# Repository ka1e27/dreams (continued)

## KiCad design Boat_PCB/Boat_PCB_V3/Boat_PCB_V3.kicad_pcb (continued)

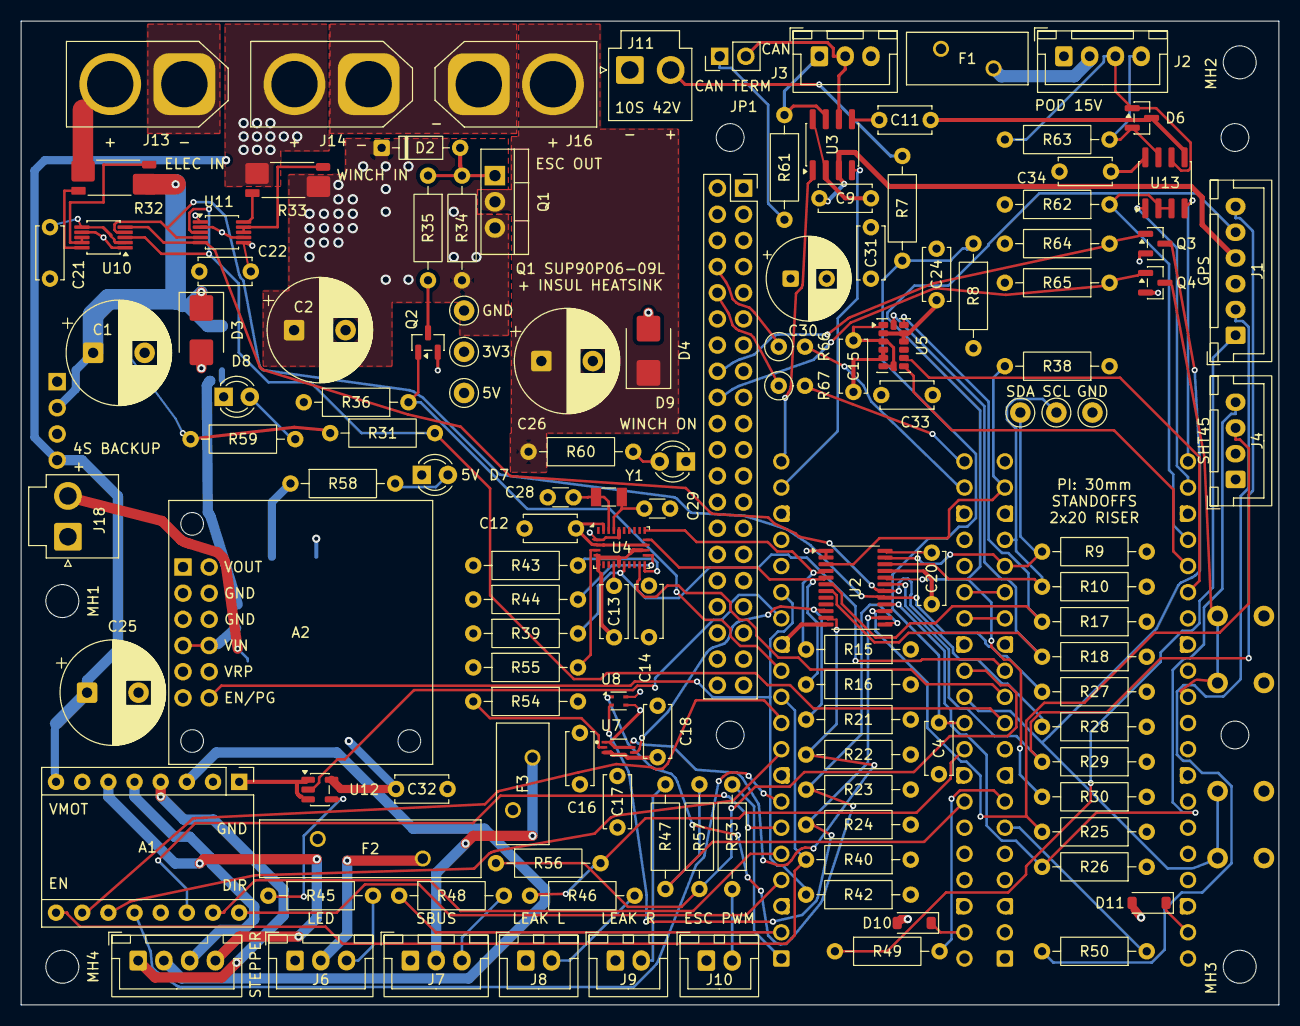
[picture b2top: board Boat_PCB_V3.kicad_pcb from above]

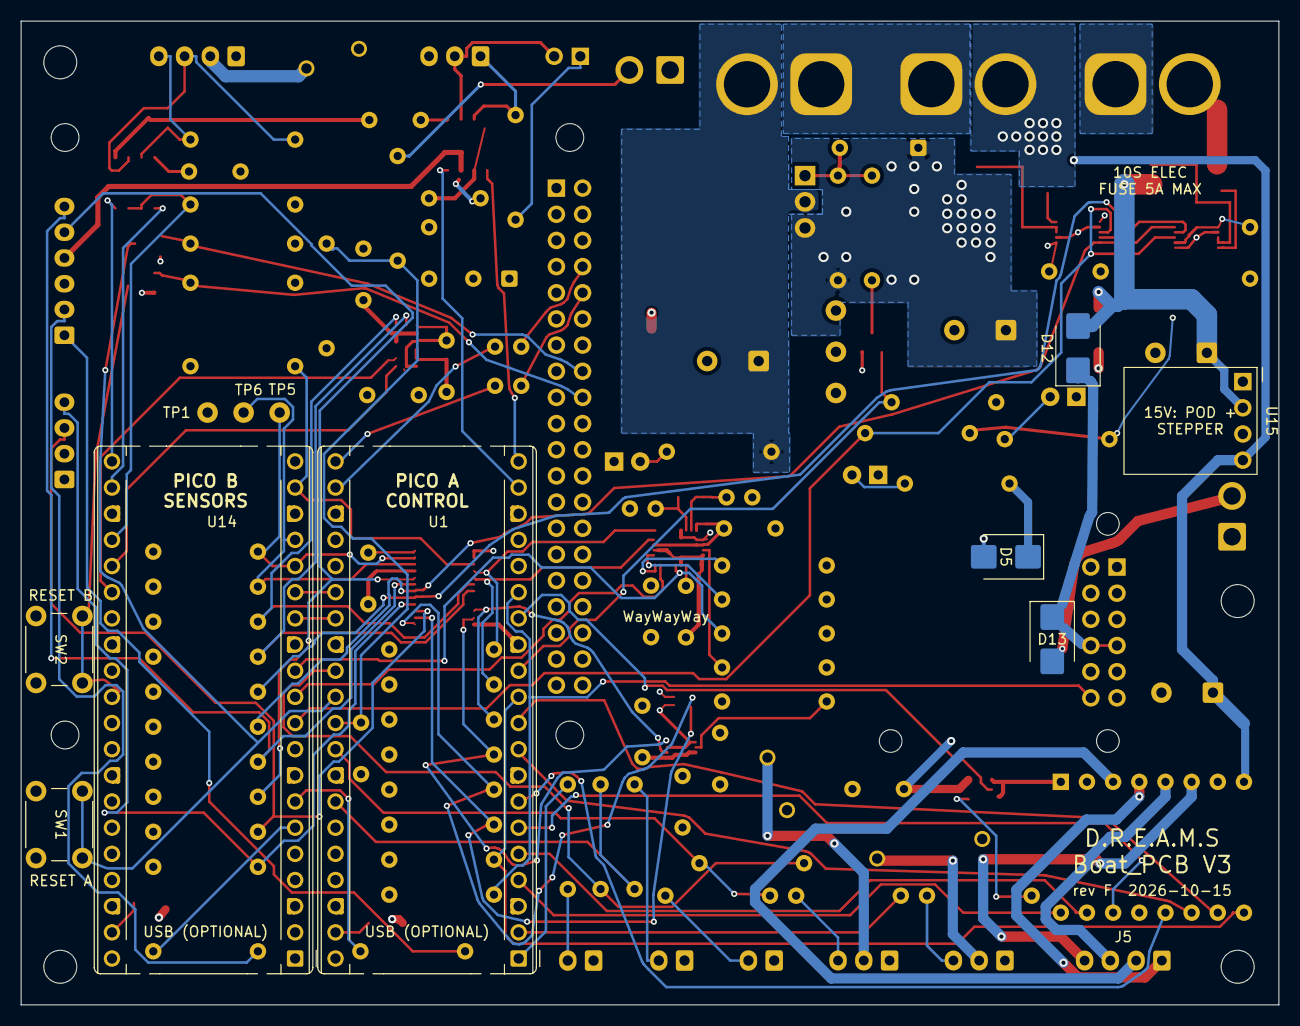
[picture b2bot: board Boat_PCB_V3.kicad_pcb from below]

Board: 4 copper layers, 122.1 x 95.5 mm, 140 parts (8 on the bottom side), 105 nets.

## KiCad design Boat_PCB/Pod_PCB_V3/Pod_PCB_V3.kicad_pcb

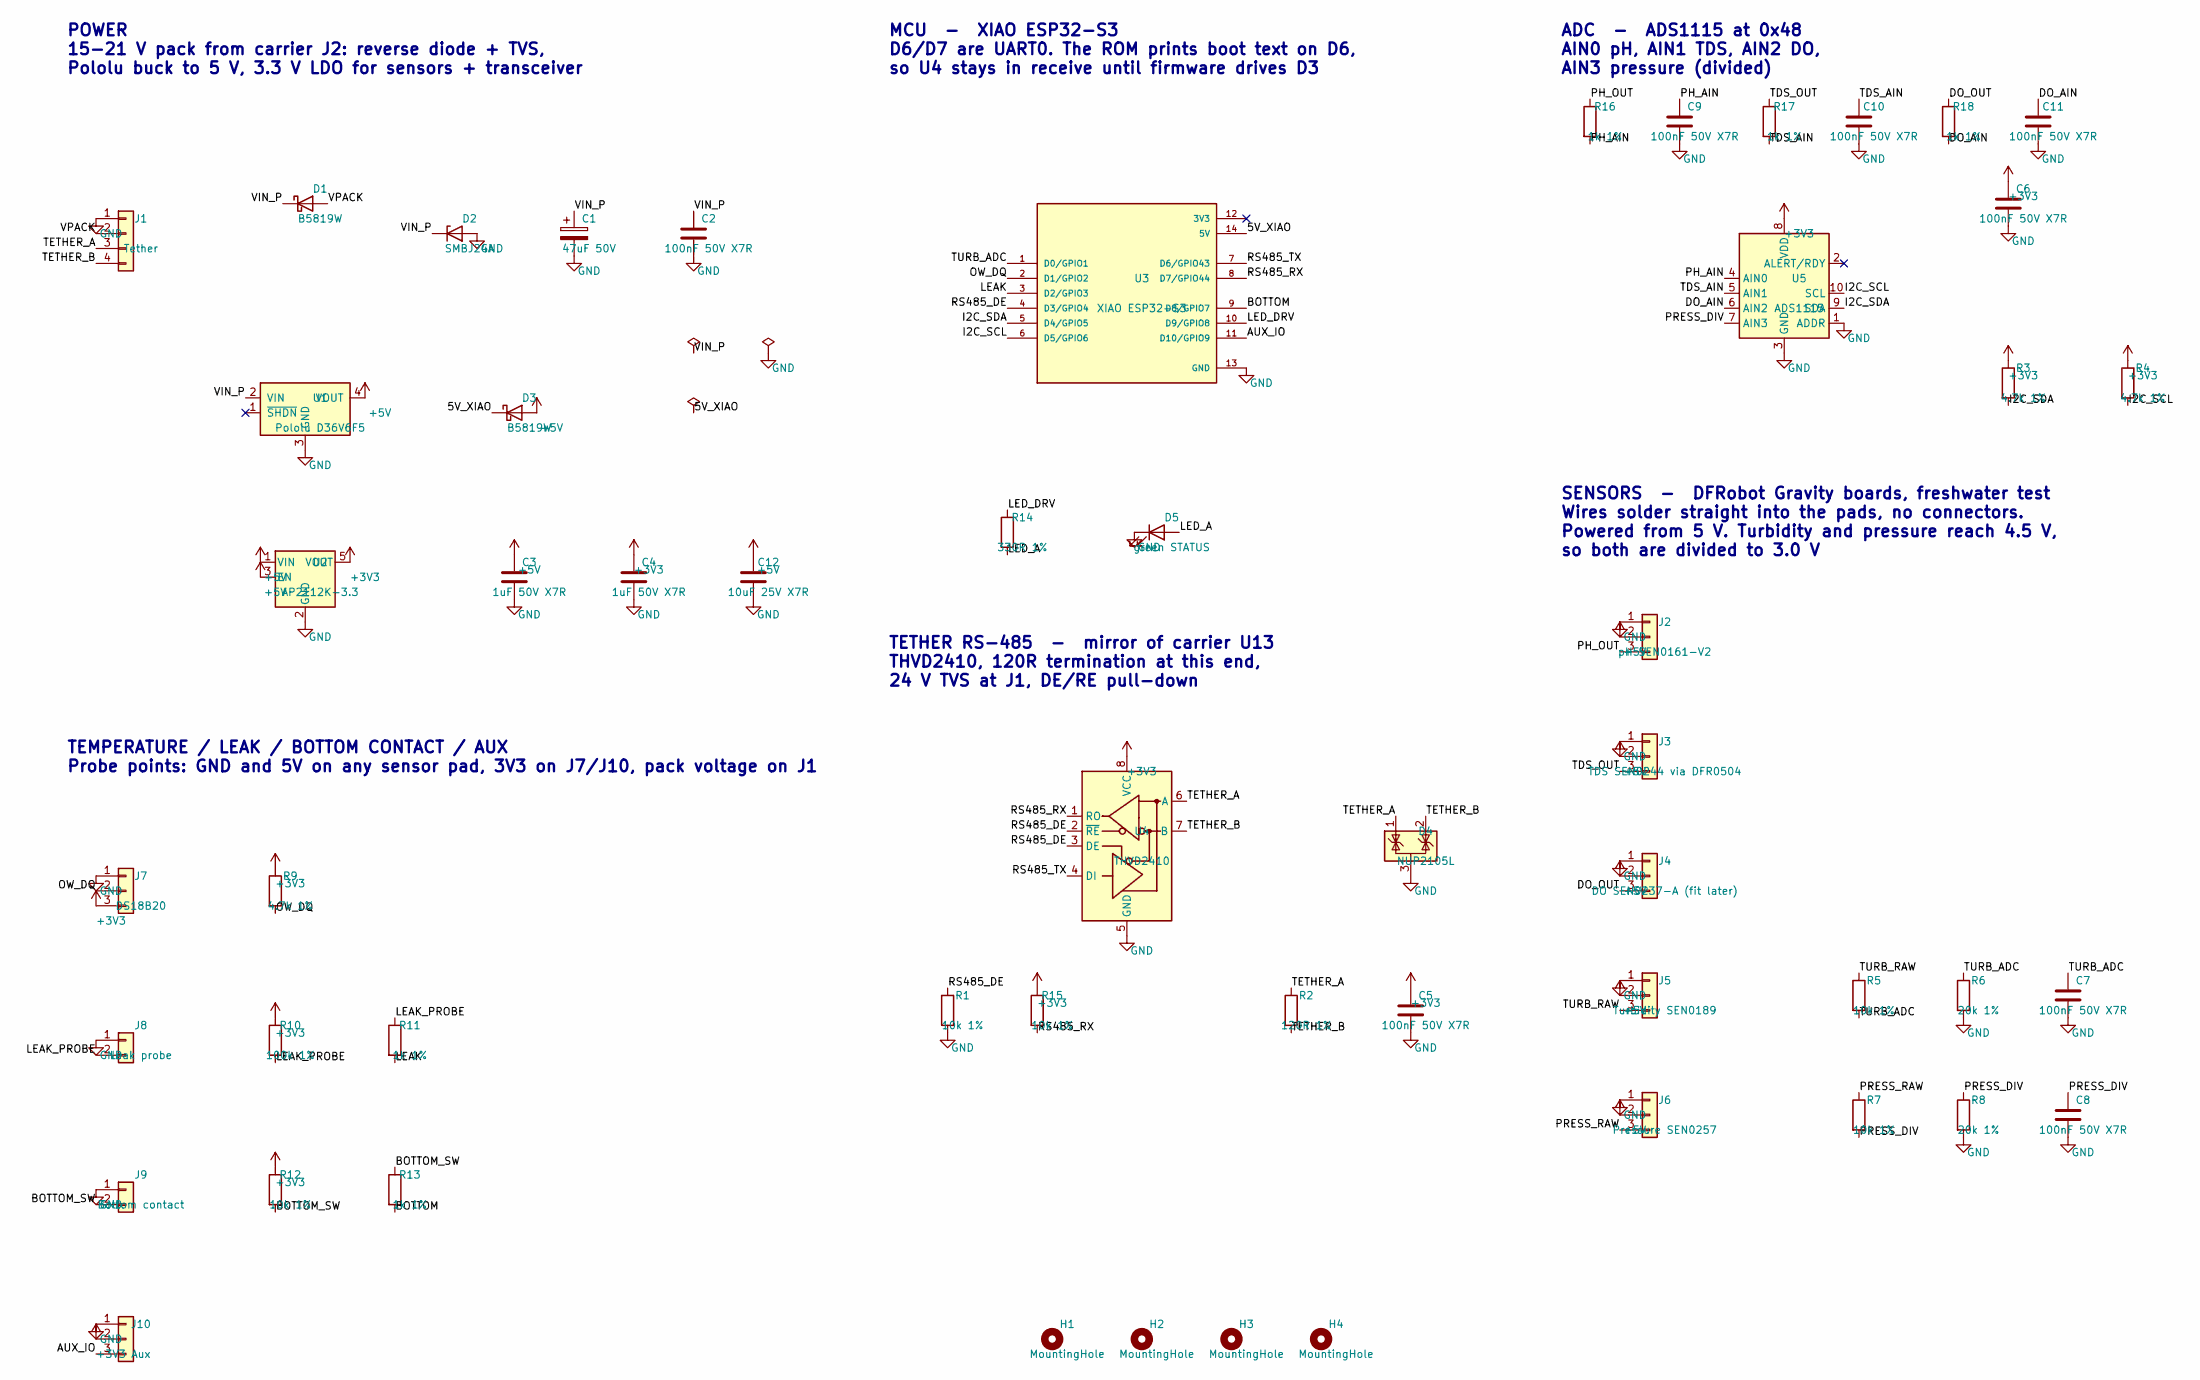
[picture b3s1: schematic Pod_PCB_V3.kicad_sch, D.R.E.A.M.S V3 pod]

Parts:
C1: 47uF 50V; CP_Radial_D6.3mm_P2.50mm
C2, C5, C6, C7, C8, C9, C10, C11: 100nF 50V X7R; C_Disc_D5.0mm_W2.5mm_P5.00mm
C3, C4: 1uF 50V X7R; C_Disc_D5.0mm_W2.5mm_P5.00mm
C12: 10uF 25V X7R; C_Disc_D5.0mm_W2.5mm_P5.00mm
D1, D3: B5819W; D_SOD-123
D2: SMBJ24A; D_SMB
D4: NUP2105L; SOT-23
D5: green STATUS; LED_D3.0mm
H1, H2, H3, H4: MountingHole; MountingHole_3.2mm_M3
J1: Tether; SolderWire_1x04_P2.54mm_D1.0mm
J2: pH SEN0161-V2; SolderWire_1x03_P2.54mm_D1.0mm
J3: TDS SEN0244 via DFR0504; SolderWire_1x03_P2.54mm_D1.0mm
J4: DO SEN0237-A (fit later); SolderWire_1x03_P2.54mm_D1.0mm
J5: Turbidity SEN0189; SolderWire_1x03_P2.54mm_D1.0mm
J6: Pressure SEN0257; SolderWire_1x03_P2.54mm_D1.0mm
J7: DS18B20; SolderWire_1x03_P2.54mm_D1.0mm
J8: Leak probe; SolderWire_1x02_P2.54mm_D1.0mm
J9: Bottom contact; SolderWire_1x02_P2.54mm_D1.0mm
J10: Aux; SolderWire_1x03_P2.54mm_D1.0mm
R1, R5, R7, R12, R15: 10k 1%; R_Axial_DIN0207_L6.3mm_D2.5mm_P10.16mm_Horizontal
R2: 120R 1%; R_Axial_DIN0207_L6.3mm_D2.5mm_P10.16mm_Horizontal
R3, R4, R9: 4.7k 1%; R_Axial_DIN0207_L6.3mm_D2.5mm_P10.16mm_Horizontal
R6, R8: 20k 1%; R_Axial_DIN0207_L6.3mm_D2.5mm_P10.16mm_Horizontal
R10: 100k 1%; R_Axial_DIN0207_L6.3mm_D2.5mm_P10.16mm_Horizontal
R11, R13, R16, R17, R18: 1k 1%; R_Axial_DIN0207_L6.3mm_D2.5mm_P10.16mm_Horizontal
R14: 330R 1%; R_Axial_DIN0207_L6.3mm_D2.5mm_P10.16mm_Horizontal
U1: Pololu D36V6F5; Pololu_D36V6F5
U2: AP2112K-3.3; SOT-23-5
U3: XIAO ESP32-S3; MODULE_XIAO_ESP32_S3
U4: THVD2410; SOIC-8_3.9x4.9mm_P1.27mm
U5: ADS1115; MSOP-10_3x3mm_P0.5mm

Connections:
+3V3: C4.1, C5.1, C6.1, J7.3 (VDD), J10.2 (3V3), R3.1, R4.1, R9.1, R10.1, R12.1, R15.1, U2.5 (VOUT), U4.8 (VCC), U5.8 (VDD)
+5V: C3.1, C12.1, D3.2 (A), J2.2 (VCC), J3.2 (VCC), J4.2 (VCC), J5.2 (VCC), J6.2 (VCC), U1.4 (VOUT), U2.1 (VIN), U2.3 (EN)
/5V_XIAO: D3.1 (K), U3.14 (5V)
/AUX_IO: J10.3 (IO), U3.11 (D10/GPIO9)
/BOTTOM: R13.2, U3.9 (D8/GPIO7)
/BOTTOM_SW: J9.2 (SW), R12.2, R13.1
/DO_AIN: C11.1, R18.2, U5.6 (AIN2)
/DO_OUT: J4.3 (SIG), R18.1
/I2C_SCL: R4.2, U3.6 (D5/GPIO6), U5.10 (SCL)
/I2C_SDA: R3.2, U3.5 (D4/GPIO5), U5.9 (SDA)
/LEAK: R11.2, U3.3 (D2/GPIO3)
/LEAK_PROBE: J8.2 (LEAK), R10.2, R11.1
/LED_A: D5.2 (A), R14.2
/LED_DRV: R14.1, U3.10 (D9/GPIO8)
/OW_DQ: J7.2 (DQ), R9.2, U3.2 (D1/GPIO2)
/PH_AIN: C9.1, R16.2, U5.4 (AIN0)
/PH_OUT: J2.3 (SIG), R16.1
/PRESS_DIV: C8.1, R7.2, R8.1, U5.7 (AIN3)
/PRESS_RAW: J6.3 (SIG), R7.1
/RS485_DE: R1.1, U3.4 (D3/GPIO4), U4.2 (~RE), U4.3 (DE)
/RS485_RX: R15.2, U3.8 (D7/GPIO44), U4.1 (RO)
/RS485_TX: U3.7 (D6/GPIO43), U4.4 (DI)
/TDS_AIN: C10.1, R17.2, U5.5 (AIN1)
/TDS_OUT: J3.3 (SIG), R17.1
/TETHER_A: D4.1 (K), J1.3 (A), R2.1, U4.6 (A)
/TETHER_B: D4.2 (K), J1.4 (B), R2.2, U4.7 (B)
/TURB_ADC: C7.1, R5.2, R6.1, U3.1 (D0/GPIO1)
/TURB_RAW: J5.3 (SIG), R5.1
/VIN_P: C1.1, C2.1, D1.1 (K), D2.1 (K), U1.2 (VIN)
/VPACK: D1.2 (A), J1.2 (VPACK)
GND: C1.2, C2.2, C3.2, C4.2, C5.2, C6.2, C7.2, C8.2, C9.2, C10.2, C11.2, C12.2, D2.2 (A), D4.3 (A), D5.1 (K), J1.1 (GND), J2.1 (GND), J3.1 (GND), J4.1 (GND), J5.1 (GND), J6.1 (GND), J7.1 (GND), J8.1 (GND), J9.1 (GND), J10.1 (GND), R1.2, R6.2, R8.2, U1.3 (GND), U2.2 (GND), U3.13 (GND), U4.5 (GND), U5.1 (ADDR), U5.3 (GND)

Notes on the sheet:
POWER 15-21 V pack from carrier J2: reverse diode + TVS, Pololu buck to 5 V, 3.3 V LDO for sensors + transceiver
MCU - XIAO ESP32-S3 D6/D7 are UART0. The ROM prints boot text on D6, so U4 stays in receive until firmware drives D3
TETHER RS-485 - mirror of carrier U13 THVD2410, 120R termination at this end, 24 V TVS at J1, DE/RE pull-down
ADC - ADS1115 at 0x48 AIN0 pH, AIN1 TDS, AIN2 DO, AIN3 pressure (divided)
SENSORS - DFRobot Gravity boards, freshwater test Wires solder straight into the pads, no connectors. Powered from 5 V. Turbidity and pressure reach 4.5 V, so both are divided to 3.0 V
TEMPERATURE / LEAK / BOTTOM CONTACT / AUX Probe points: GND and 5V on any sensor pad, 3V3 on J7/J10, pack voltage on J1

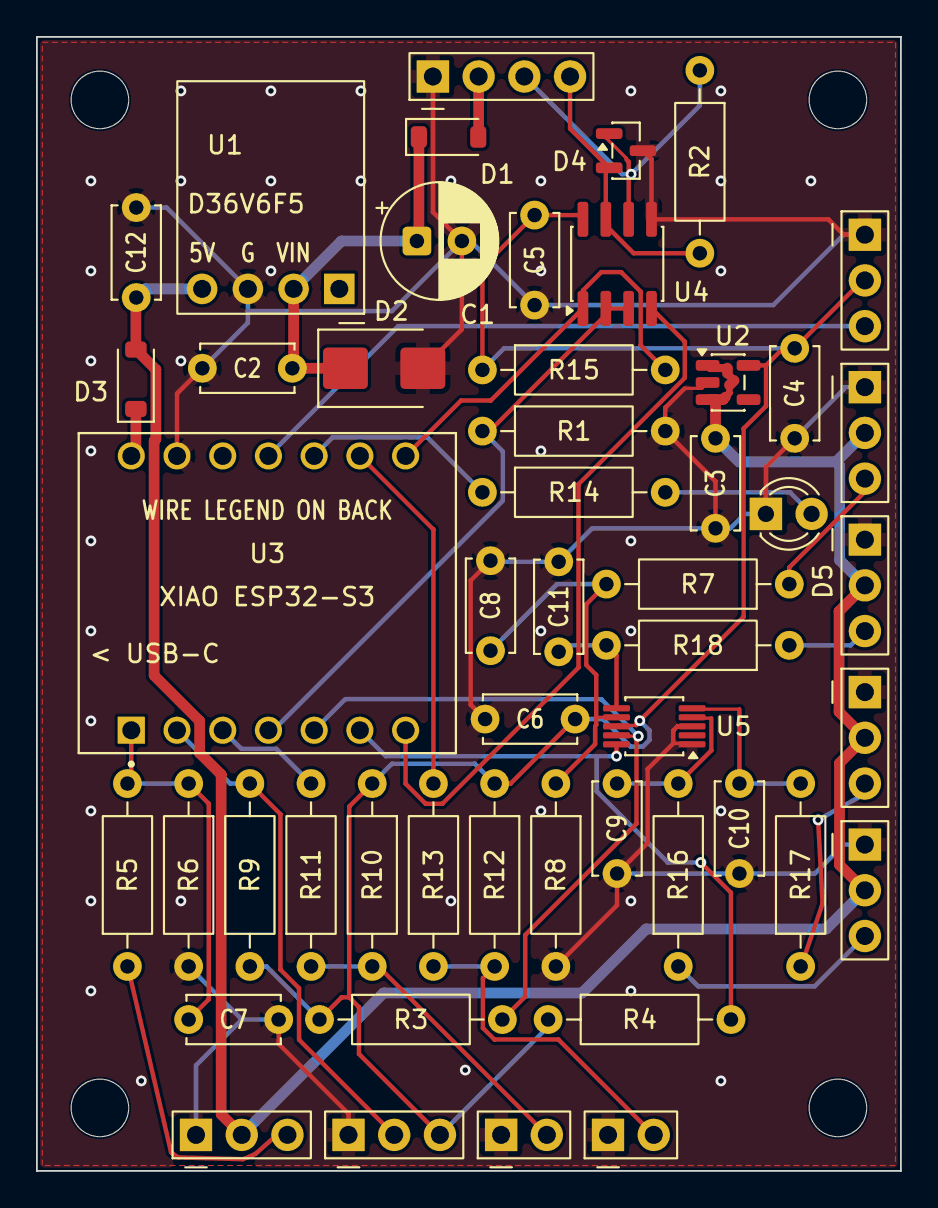
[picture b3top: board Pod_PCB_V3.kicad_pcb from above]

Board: 2 copper layers, 48.0 x 63.0 mm, 54 parts (0 on the bottom side), 31 nets.

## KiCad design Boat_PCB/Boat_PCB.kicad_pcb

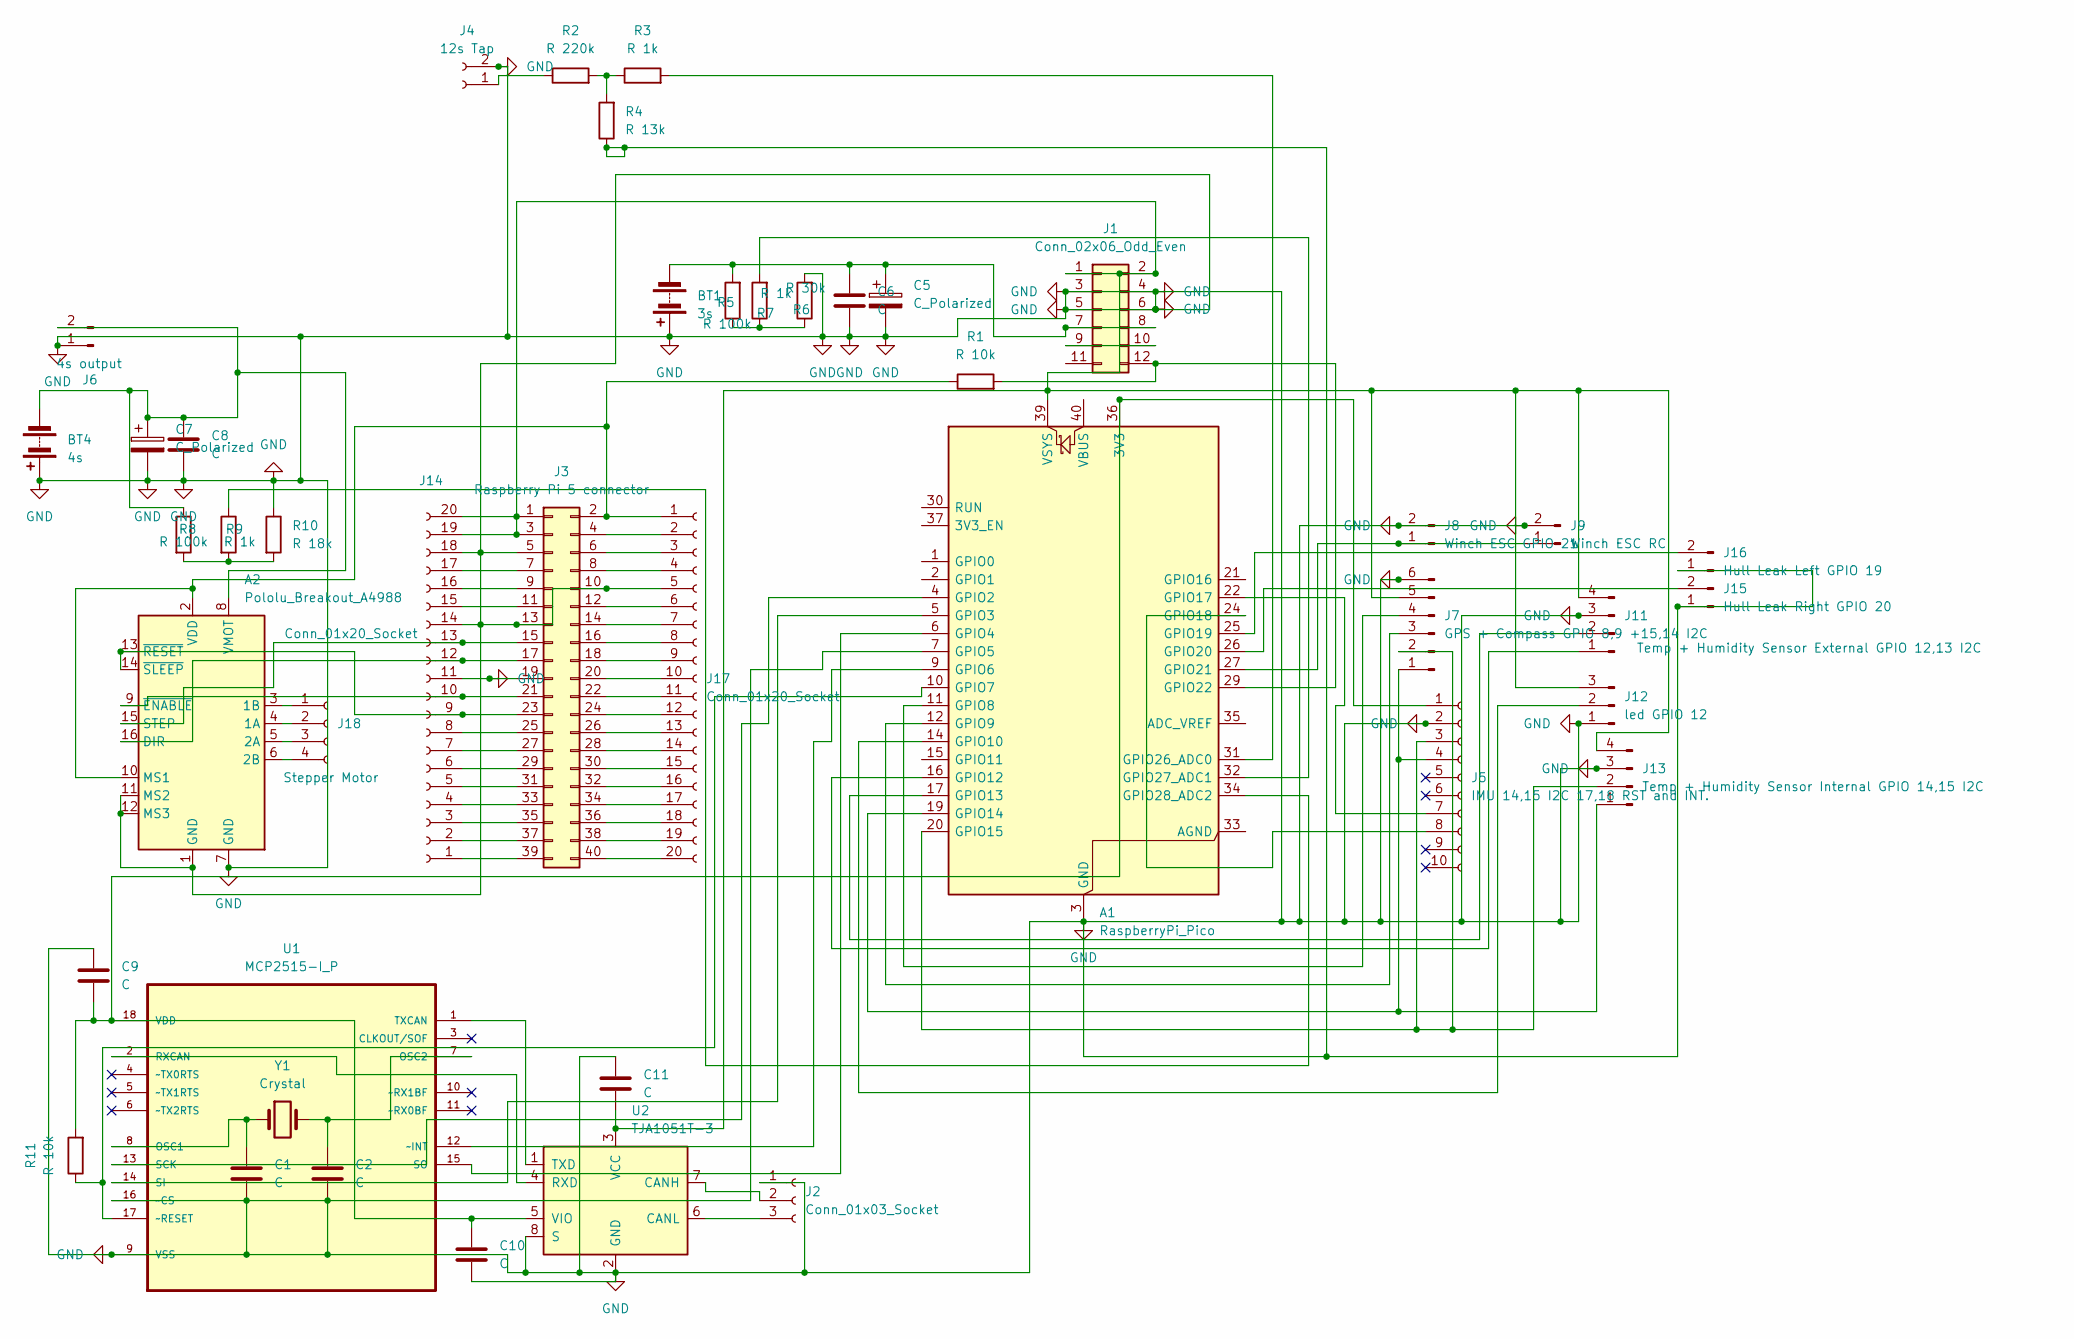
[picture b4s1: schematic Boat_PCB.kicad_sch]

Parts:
A1: RaspberryPi_Pico; Raspberry pico no antenna
A2: Pololu_Breakout_A4988; Pololu_Breakout-16_15.2x20.3mm
BT1: 3s; AMASS_XT60-M_1x02_P7.20mm_Vertical
BT4: 4s; AMASS_XT60-M_1x02_P7.20mm_Vertical
C1, C2: C; C_Disc_D3.0mm_W1.6mm_P2.50mm
C5, C7: C_Polarized; CP_Radial_D10.0mm_P5.00mm
C6, C8, C9, C10, C11: C; C_Disc_D5.0mm_W2.5mm_P5.00mm
J1: Conn_02x06_Odd_Even; Pololu 36v5vstepdown
J2: Conn_01x03_Socket; JST_XH_B3B-XH-A_1x03_P2.50mm_Vertical
J3: Raspberry Pi 5 connector; Raspberry Pi Mounting
J4: 12s Tap; JST_XH_B2B-XH-A_1x02_P2.50mm_Vertical
J5: IMU 14,15 I2C 17,18 RST and INT.; JST_XH_B10B-XH-A_1x10_P2.50mm_Vertical
J6: 4s output; AMASS_XT60-M_1x02_P7.20mm_Vertical
J7: GPS + Compass GPIO 8,9 +15,14 I2C; JST_XH_B6B-XH-A_1x06_P2.50mm_Vertical
J8: Winch ESC GPIO 21; JST_XH_B2B-XH-A_1x02_P2.50mm_Vertical
J9: Winch ESC RC; PinSocket_1x02_P2.54mm_Vertical
J11: Temp + Humidity Sensor External GPIO 12,13 I2C; JST_XH_B4B-XH-A_1x04_P2.50mm_Vertical
J12: led GPIO 12; JST_XH_B3B-XH-A_1x03_P2.50mm_Vertical
J13: Temp + Humidity Sensor Internal GPIO 14,15 I2C; PinHeader_1x04_P2.54mm_Vertical
J14, J17: Conn_01x20_Socket; PinSocket_1x20_P2.54mm_Vertical
J15: Hull Leak Right GPIO 20; JST_XH_B2B-XH-A_1x02_P2.50mm_Vertical
J16: Hull Leak Left GPIO 19; JST_XH_B2B-XH-A_1x02_P2.50mm_Vertical
J18: Stepper Motor; JST_XH_B4B-XH-A_1x04_P2.50mm_Vertical
R1, R11: R 10k; R_Axial_DIN0207_L6.3mm_D2.5mm_P10.16mm_Horizontal
R2: R 220k; R_Axial_DIN0207_L6.3mm_D2.5mm_P10.16mm_Horizontal
R3, R7, R9: R 1k; R_Axial_DIN0207_L6.3mm_D2.5mm_P10.16mm_Horizontal
R4: R 13k; R_Axial_DIN0207_L6.3mm_D2.5mm_P10.16mm_Horizontal
R5, R8: R 100k; R_Axial_DIN0207_L6.3mm_D2.5mm_P10.16mm_Horizontal
R6: R 30k; R_Axial_DIN0207_L6.3mm_D2.5mm_P10.16mm_Horizontal
R10: R 18k; R_Axial_DIN0207_L6.3mm_D2.5mm_P10.16mm_Horizontal
U1: MCP2515-I_P; DIP254P762X432-18; MPN MCP2515-I/P
U2: TJA1051T-3; SOIC-8_3.9x4.9mm_P1.27mm
Y1: Crystal; Crystal_HC49-4H_Vertical

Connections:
GND: A1.3 (GND), A1.7 (GPIO5), A1.8 (GND), A1.13 (GND), A1.18 (GND), A1.23 (GND), A1.28 (GND), A1.38 (GND), A2.1 (GND), A2.7 (GND), A2.11 (MS2), A2.12 (MS3), BT1.1 (+), BT4.1 (+), C1.1, C2.1, C5.2, C6.2, C7.2, C8.2, C9.1, C10.2, C11.1, J1.3, J1.4, J1.5, J1.6, J2.1, J3.5, J3.10, J3.13, J3.19, J4.2, J5.2, J6.1, J7.6, J8.2, J9.2, J11.3, J12.1, J13.3, J14.11, J14.14, J14.18, J15.1, J16.1, J17.5, R4.1, R6.2, R10.1, U1.9 (VSS), U1.16 (~CS), U2.2 (GND), U2.8 (S)
unnamed: A1.36 (3V3), C9.2, C10.1, J5.1, R11.2, U1.18 (VDD), U2.5 (VIO)
unnamed: A1.4 (GPIO2), U1.13 (SCK)
unnamed: A1.5 (GPIO3), U1.14 (SI)
unnamed: A1.6 (GPIO4), U1.15 (SO)
unnamed: A1.9 (GPIO6), U1.12 (~INT)
unnamed: A1.10 (GPIO7), R11.1, U1.17 (~RESET)
unnamed: A1.11 (GPIO8), J7.4
unnamed: A1.12 (GPIO9), J7.3
unnamed: A1.14 (GPIO10), J12.2
unnamed: A1.16 (GPIO12), J11.1
unnamed: A1.17 (GPIO13), J11.2
unnamed: A1.19 (GPIO14), J5.4, J7.1, J13.1
unnamed: A1.20 (GPIO15), J5.3, J7.2, J13.2
unnamed: A1.22 (GPIO17), J5.7
unnamed: A1.24 (GPIO18), J5.8
unnamed: A1.25 (GPIO19), J16.2
unnamed: A1.26 (GPIO20), J15.2
unnamed: A1.27 (GPIO21), J8.1, J9.1
unnamed: A1.29 (GPIO22), J1.12, R1.2
unnamed: A1.31 (GPIO26_ADC0), R3.2
unnamed: A1.32 (GPIO27_ADC1), R7.2
unnamed: A1.34 (GPIO28_ADC2), R9.1
unnamed: A1.39 (VSYS), C11.2, J1.1, J1.2, J3.1, J3.3, J7.5, J11.4, J12.3, J13.4, J14.19, J14.20, U2.3 (VCC)
unnamed: A2.4 (1A), J18.2
unnamed: A2.3 (1B), J18.1
unnamed: A2.5 (2A), J18.3
unnamed: A2.6 (2B), J18.4
unnamed: A2.16 (DIR), J3.17, J14.12
unnamed: A2.2 (VDD), A2.10 (MS1), J3.2, J17.1, R1.1
unnamed: A2.15 (STEP), J3.15, J14.13
unnamed: A2.8 (VMOT), BT4.2 (-), C7.1, C8.1, J6.2, R8.1
unnamed: A2.9 (~ENABLE), J3.21, J14.10
unnamed: A2.13 (~RESET), A2.14 (~SLEEP), J3.23, J14.9
unnamed: BT1.2 (-), C5.1, C6.1, J1.7, J1.8, R5.2
unnamed: J1.9, J1.10
unnamed: J2.2, U2.7 (CANH)
unnamed: J2.3, U2.6 (CANL)
unnamed: J4.1, R2.1
unnamed: J3.39, J14.1
unnamed: J3.37, J14.2
unnamed: J3.35, J14.3
unnamed: J3.33, J14.4
unnamed: J3.31, J14.5
unnamed: J3.29, J14.6
unnamed: J3.27, J14.7
unnamed: J3.25, J14.8
unnamed: J3.11, J14.15
unnamed: J3.9, J14.16
unnamed: J3.7, J14.17
unnamed: J3.4, J17.2
unnamed: J3.6, J17.3
unnamed: J3.8, J17.4
unnamed: J3.12, J17.6
unnamed: J3.14, J17.7
unnamed: J3.16, J17.8
unnamed: J3.18, J17.9
unnamed: J3.20, J17.10
unnamed: J3.22, J17.11
unnamed: J3.24, J17.12
unnamed: J3.26, J17.13
unnamed: J3.28, J17.14
unnamed: J3.30, J17.15
unnamed: J3.32, J17.16
unnamed: J3.34, J17.17
unnamed: J3.36, J17.18
unnamed: J3.38, J17.19
unnamed: J3.40, J17.20
unnamed: R2.2, R3.1, R4.2
unnamed: R5.1, R6.1, R7.1
unnamed: R8.2, R9.2, R10.2
unnamed: C1.2, U1.8 (OSC1), Y1.1
unnamed: C2.2, U1.7 (OSC2), Y1.2
unnamed: U1.2 (RXCAN), U2.4 (RXD)
unnamed: U1.1 (TXCAN), U2.1 (TXD)

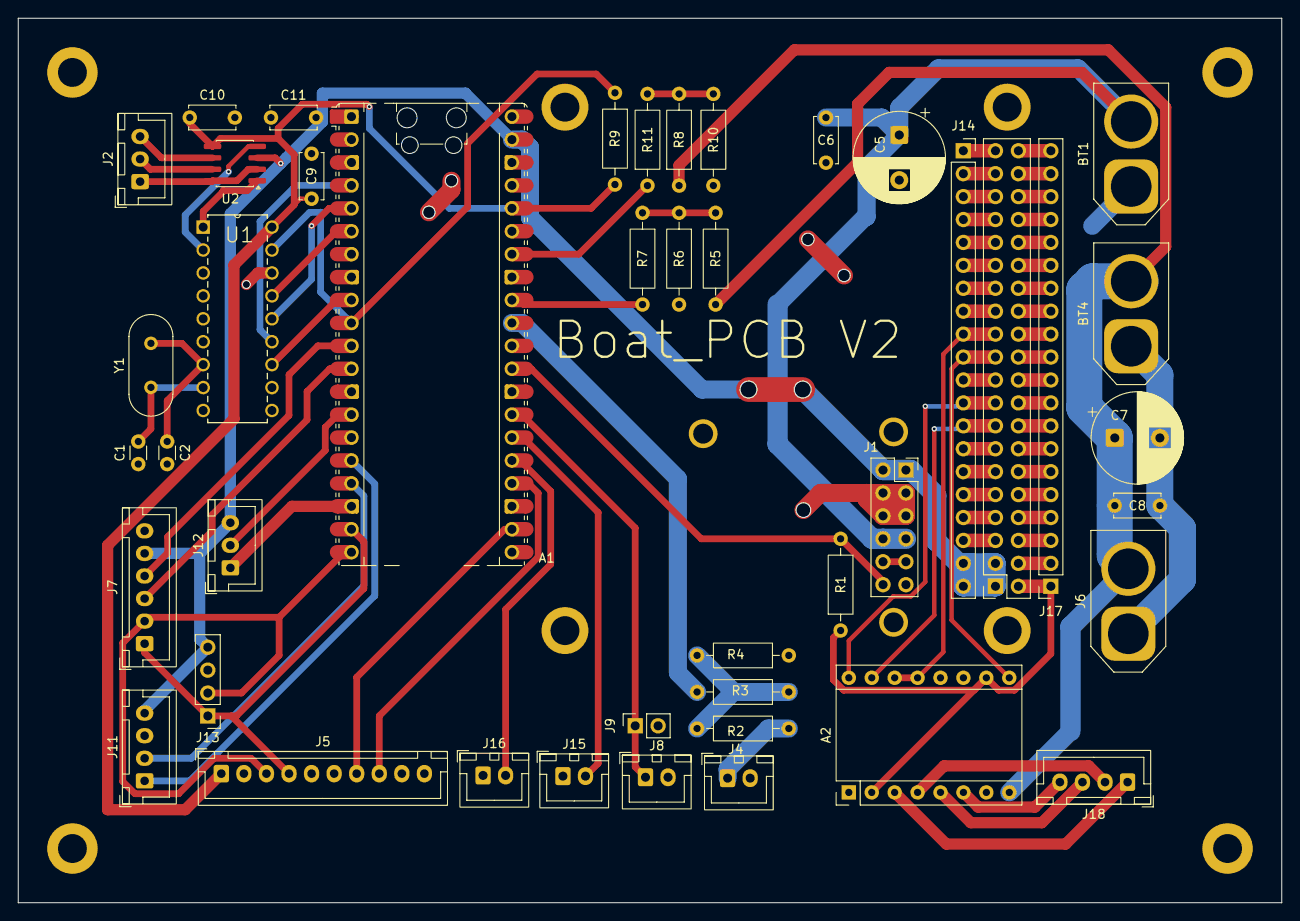
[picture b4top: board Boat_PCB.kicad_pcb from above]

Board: 2 copper layers, 140.0 x 98.0 mm, 44 parts (0 on the bottom side), 75 nets.

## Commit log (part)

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2026-04-08 Expand README with project details and instructions
    Added detailed project description, features, architecture, tech stack, getting started guide, and hardware requirements.
2026-06-10 camera id change
